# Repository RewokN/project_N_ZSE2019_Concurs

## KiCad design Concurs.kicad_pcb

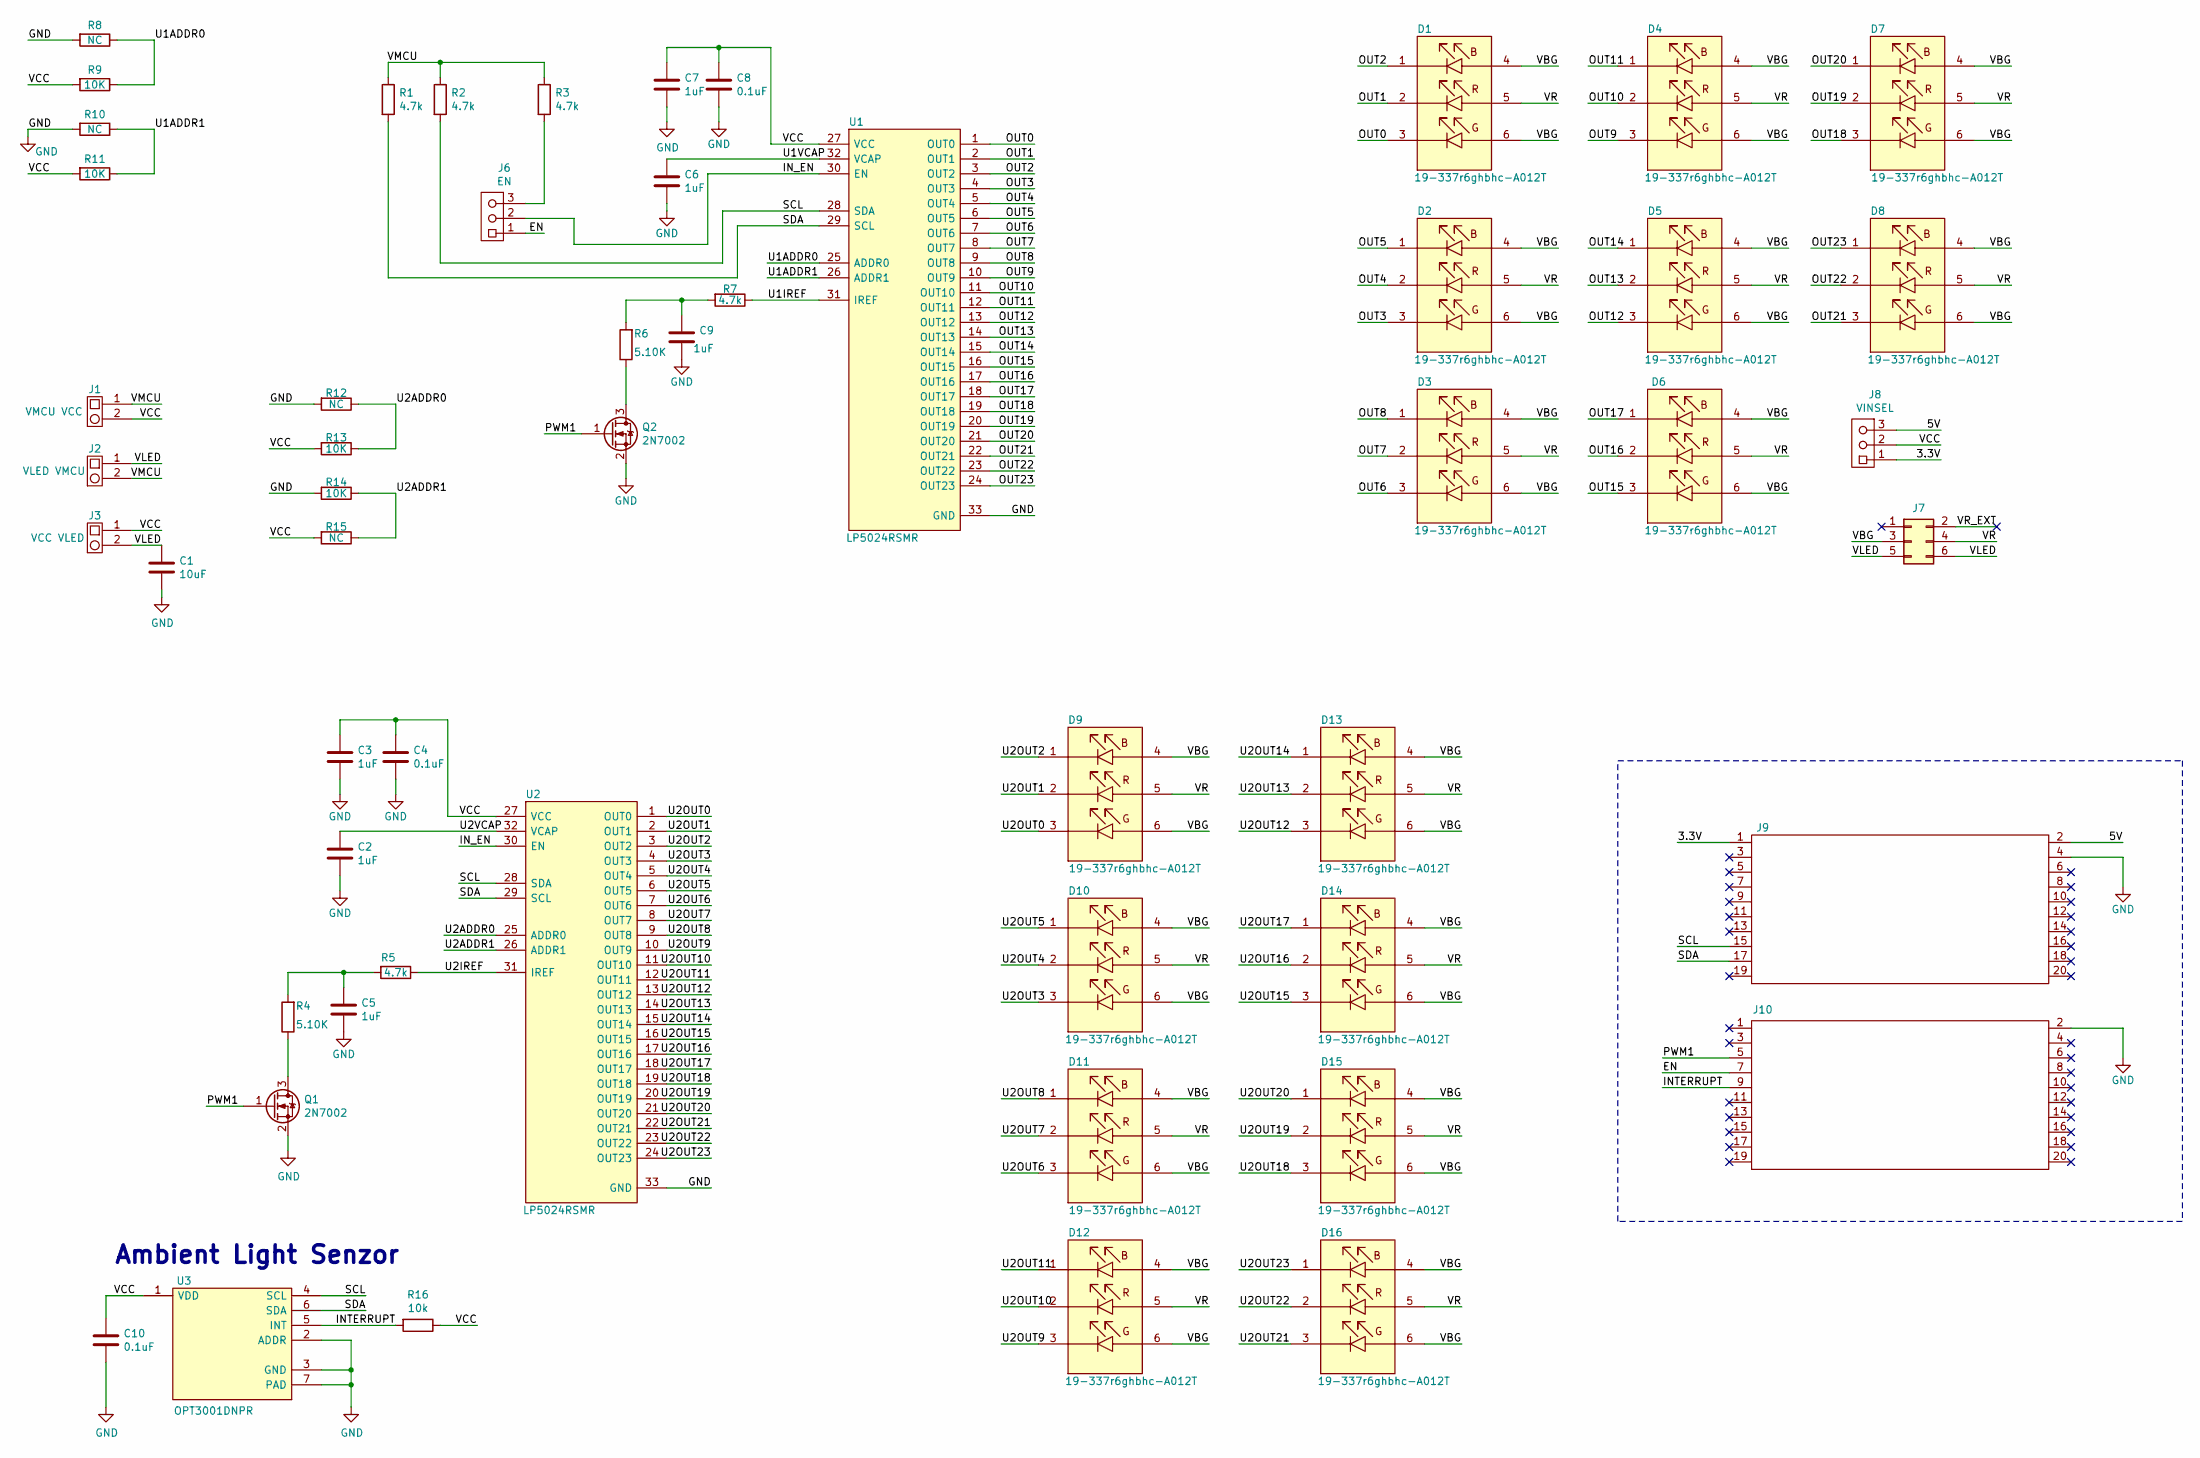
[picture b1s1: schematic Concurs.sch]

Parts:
C1: 10uF; C_0603_1608Metric
C2, C3, C5, C6, C7, C9: 1uF; C_0603_1608Metric
C4, C8, C10: 0.1uF; C_0603_1608Metric
D1, D2, D3, D4, D5, D6, D7, D8, D9, D10, D11, D12, D13, D14, D15, D16: 19-337r6ghbhc-A012T; EL-19-337_R6GHBHC-A01
J1: VMCU VCC; PinHeader_1x02_P2.54mm_Vertical
J2: VLED VMCU; PinHeader_1x02_P2.54mm_Vertical
J3: VCC VLED; PinHeader_1x02_P2.54mm_Vertical
J6: EN; PinHeader_1x03_P2.54mm_Vertical
J7: Conn_02x03_Odd_Even; PinHeader_2x03_P2.54mm_Vertical
J8: VINSEL; PinHeader_1x03_P2.54mm_Vertical
J9, J10: Conn_02x10_Odd_Even_MountingPin; PinHeader_2x10_P2.54mm_Vertical
Q1, Q2: 2N7002; SOT-23
R1, R2, R3, R5, R7: 4.7k; R_0603_1608Metric
R4, R6: 5.10K; R_0603_1608Metric
R8, R10, R12, R15: NC; R_0603_1608Metric
R9, R11, R13, R14: 10K; R_0603_1608Metric
R16: 10k; R_0603_1608Metric
U1, U2: LP5024RSMR; QFN-32-1EP_4x4mm_P0.4mm_EP2.9x2.9mm; Manufacturer_Part_Number LP5024RSMR; Mouser Part Number 595-LP5024RSMR
U3: OPT3001DNPR; opt3001; Manufacturer_Part_Number OPT3001DNPR; Mouser Part Number 595-OPT3001DNPR

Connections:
/3.3V: J8.1, J9.1
/5V: J8.3, J9.2
/EN: J6.1, J10.7
/INTERRUPT: J10.9, R16.2, U3.5 (INT)
/IN_EN: J6.2, U1.30 (EN), U2.30 (EN)
/OUT0: D1.3, U1.1 (OUT0)
/OUT1: D1.2, U1.2 (OUT1)
/OUT2: D1.1, U1.3 (OUT2)
/OUT3: D2.3, U1.4 (OUT3)
/OUT4: D2.2, U1.5 (OUT4)
/OUT5: D2.1, U1.6 (OUT5)
/OUT6: D3.3, U1.7 (OUT6)
/OUT7: D3.2, U1.8 (OUT7)
/OUT8: D3.1, U1.9 (OUT8)
/OUT9: D4.3, U1.10 (OUT9)
/OUT10: D4.2, U1.11 (OUT10)
/OUT11: D4.1, U1.12 (OUT11)
/OUT12: D5.3, U1.13 (OUT12)
/OUT13: D5.2, U1.14 (OUT13)
/OUT14: D5.1, U1.15 (OUT14)
/OUT15: D6.3, U1.16 (OUT15)
/OUT16: D6.2, U1.17 (OUT16)
/OUT17: D6.1, U1.18 (OUT17)
/OUT18: D7.3, U1.19 (OUT18)
/OUT19: D7.2, U1.20 (OUT19)
/OUT20: D7.1, U1.21 (OUT20)
/OUT21: D8.3, U1.22 (OUT21)
/OUT22: D8.2, U1.23 (OUT22)
/OUT23: D8.1, U1.24 (OUT23)
/PWM1: J10.5, Q1.1 (G), Q2.1 (G)
/SCL: J9.15, R2.2, U1.28 (SDA), U2.28 (SDA), U3.4 (SCL)
/SDA: J9.17, R1.2, U1.29 (SCL), U2.29 (SCL), U3.6 (SDA)
/U1ADDR0: R8.1, R9.1, U1.25 (ADDR0)
/U1ADDR1: R10.1, R11.1, U1.26 (ADDR1)
/U1IREF: R7.1, U1.31 (IREF)
/U1VCAP: C6.1, U1.32 (VCAP)
/U2ADDR0: R12.1, R13.1, U2.25 (ADDR0)
/U2ADDR1: R14.1, R15.1, U2.26 (ADDR1)
/U2IREF: R5.1, U2.31 (IREF)
/U2OUT0: D9.3, U2.1 (OUT0)
/U2OUT1: D9.2, U2.2 (OUT1)
/U2OUT2: D9.1, U2.3 (OUT2)
/U2OUT3: D10.3, U2.4 (OUT3)
/U2OUT4: D10.2, U2.5 (OUT4)
/U2OUT5: D10.1, U2.6 (OUT5)
/U2OUT6: D11.3, U2.7 (OUT6)
/U2OUT7: D11.2, U2.8 (OUT7)
/U2OUT8: D11.1, U2.9 (OUT8)
/U2OUT9: D12.3, U2.10 (OUT9)
/U2OUT10: D12.2, U2.11 (OUT10)
/U2OUT11: D12.1, U2.12 (OUT11)
/U2OUT12: D13.3, U2.13 (OUT12)
/U2OUT13: D13.2, U2.14 (OUT13)
/U2OUT14: D13.1, U2.15 (OUT14)
/U2OUT15: D14.3, U2.16 (OUT15)
/U2OUT16: D14.2, U2.17 (OUT16)
/U2OUT17: D14.1, U2.18 (OUT17)
/U2OUT18: D15.3, U2.19 (OUT18)
/U2OUT19: D15.2, U2.20 (OUT19)
/U2OUT20: D15.1, U2.21 (OUT20)
/U2OUT21: D16.3, U2.22 (OUT21)
/U2OUT22: D16.2, U2.23 (OUT22)
/U2OUT23: D16.1, U2.24 (OUT23)
/U2VCAP: C2.1, U2.32 (VCAP)
/VBG: D1.4, D1.6, D2.4, D2.6, D3.4, D3.6, D4.4, D4.6, D5.4, D5.6, D6.4, D6.6, D7.4, D7.6, D8.4, D8.6, D9.4, D9.6, D10.4, D10.6, D11.4, D11.6, D12.4, D12.6, D13.4, D13.6, D14.4, D14.6, D15.4, D15.6, D16.4, D16.6, J7.3
/VCC: C3.1, C4.1, C7.1, C8.1, C10.1, J1.2, J3.1, J8.2, R9.2, R11.2, R13.2, R15.2, R16.1, U1.27 (VCC), U2.27 (VCC), U3.1 (VDD)
/VLED: C1.1, J2.1, J3.2, J7.5, J7.6
/VMCU: J1.1, J2.2, R1.1, R2.1, R3.1
/VR: D1.5, D2.5, D3.5, D4.5, D5.5, D6.5, D7.5, D8.5, D9.5, D10.5, D11.5, D12.5, D13.5, D14.5, D15.5, D16.5, J7.4
/VR_EXT: J7.2
GND: C1.2, C2.2, C3.2, C4.2, C5.2, C6.2, C7.2, C8.2, C9.2, C10.2, J9.4, J10.2, Q1.2 (S), Q2.2 (S), R8.2, R10.2, R12.2, R14.2, U1.33 (GND), U2.33 (GND), U3.2 (ADDR), U3.3 (GND), U3.7 (PAD)
unnamed: C5.1, R4.2, R5.2
unnamed: C9.1, R6.2, R7.2
unnamed: J6.3, R3.2
unnamed: Q1.3 (D), R4.1
unnamed: Q2.3 (D), R6.1

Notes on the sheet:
Ambient Light Senzor

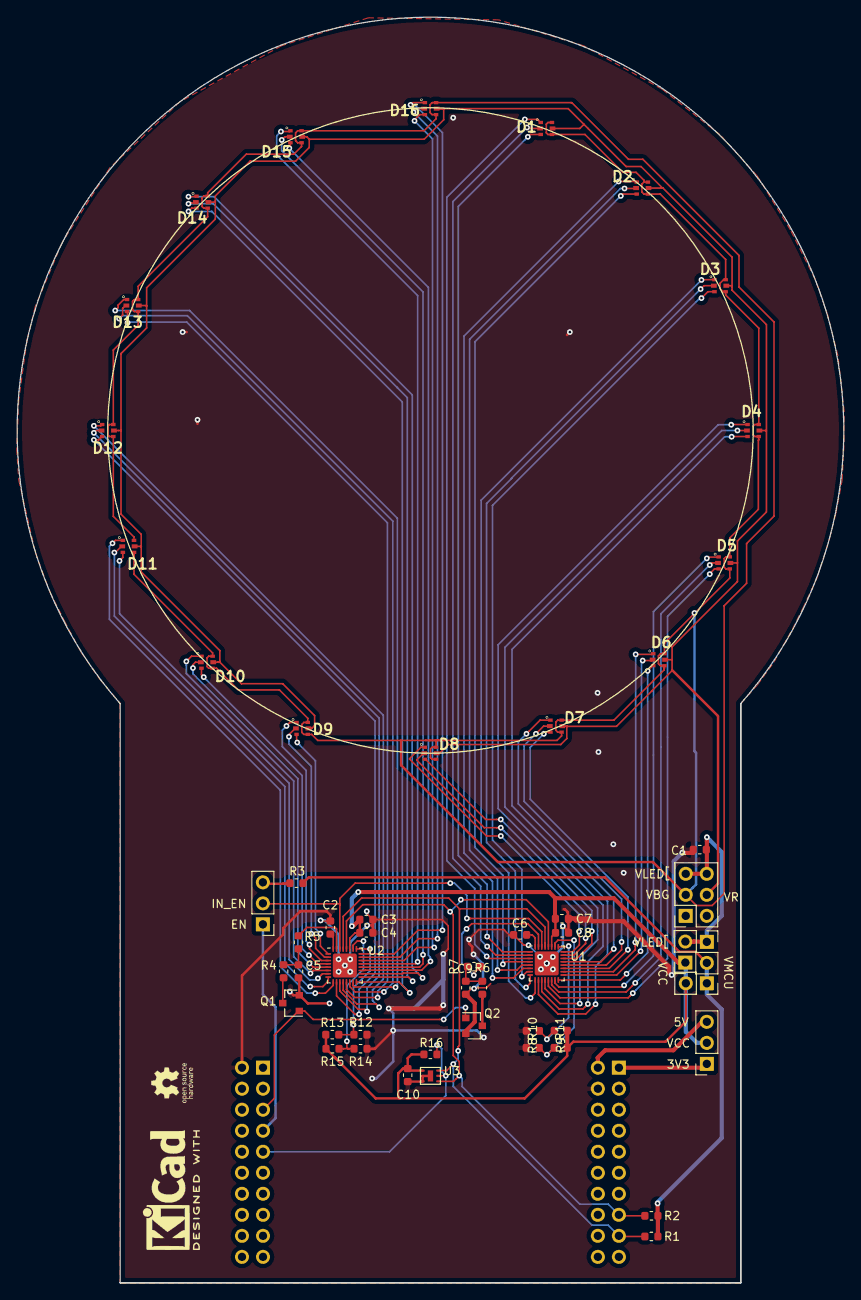
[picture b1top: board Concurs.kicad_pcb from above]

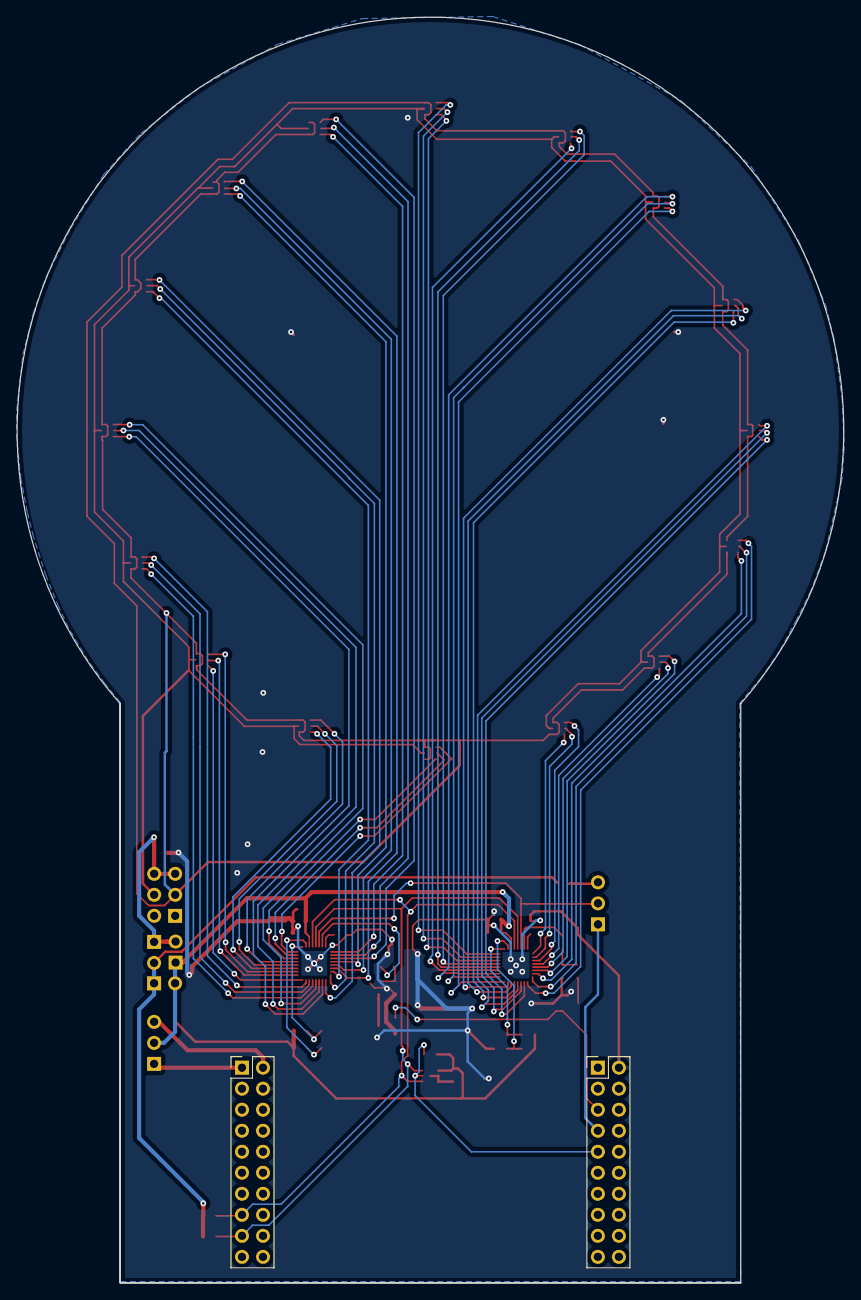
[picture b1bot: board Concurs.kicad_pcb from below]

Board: 2 copper layers, 99.9 x 153.0 mm, 55 parts (2 on the bottom side), 75 nets.
